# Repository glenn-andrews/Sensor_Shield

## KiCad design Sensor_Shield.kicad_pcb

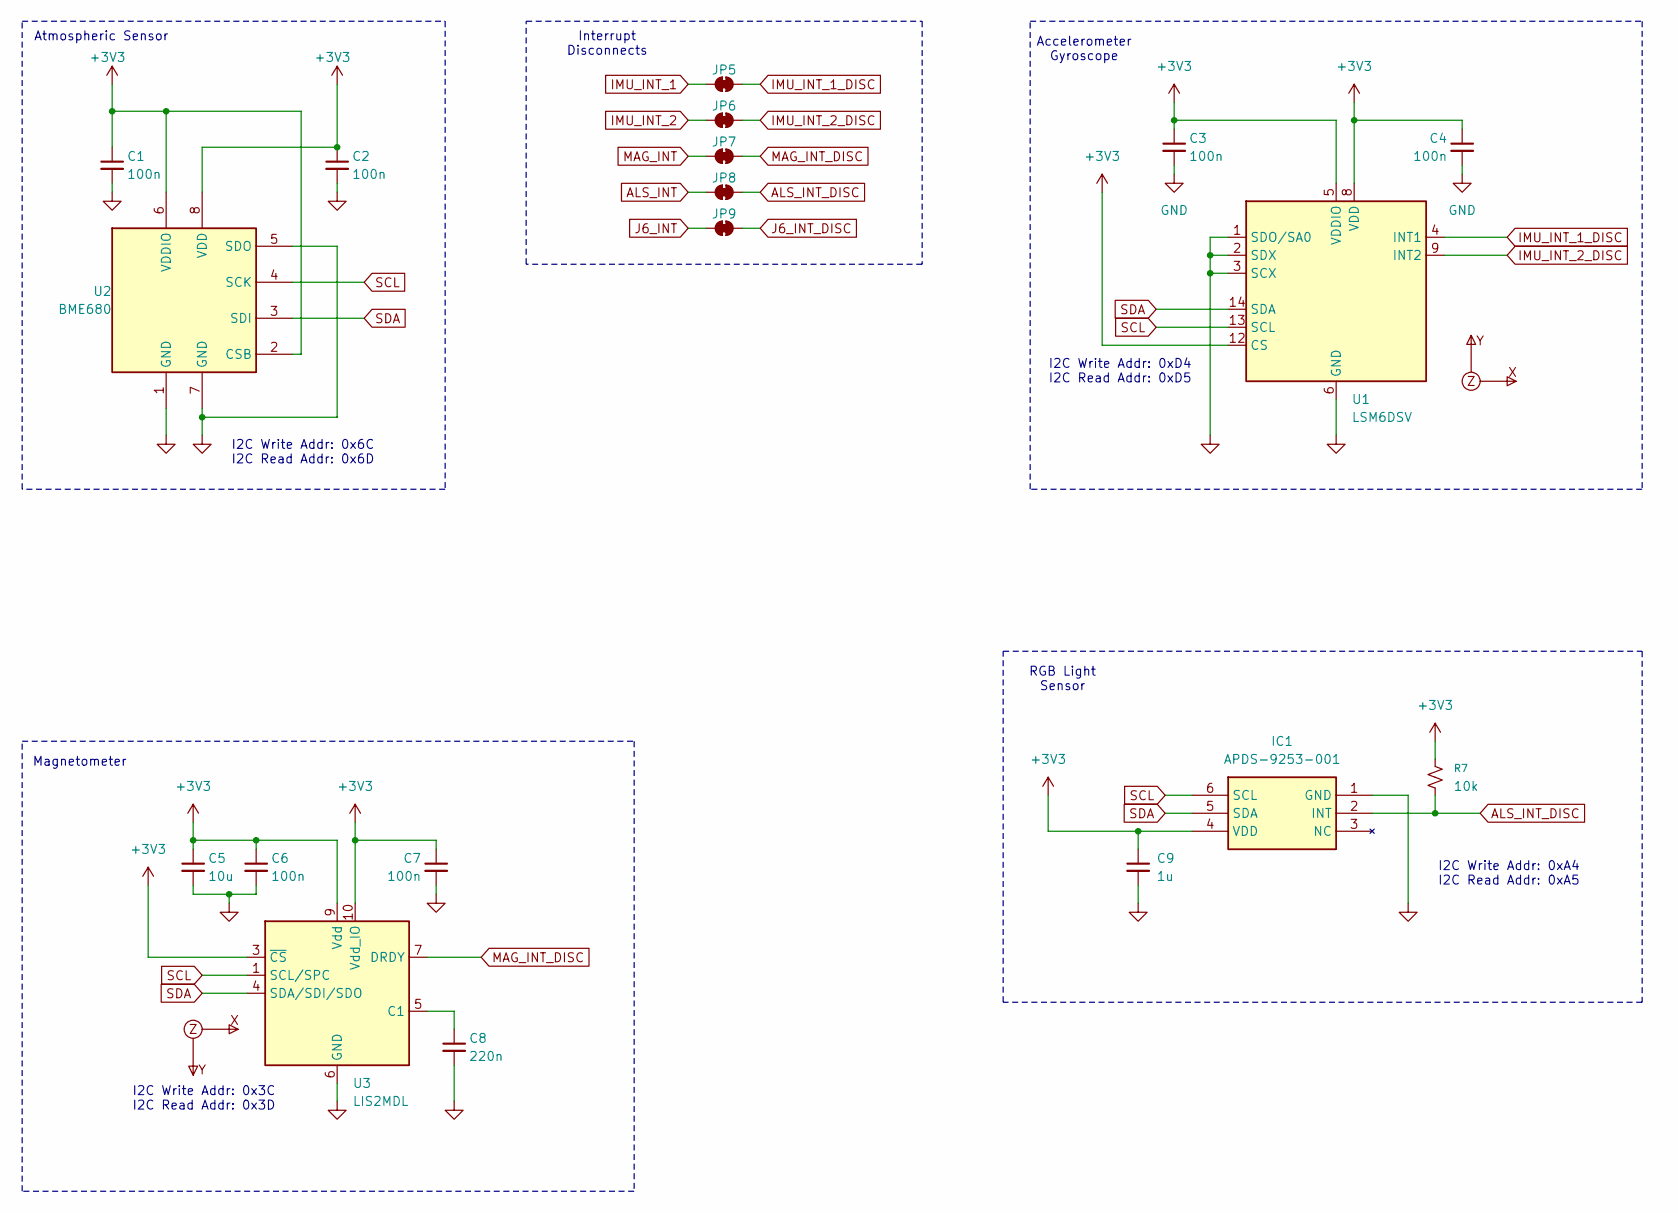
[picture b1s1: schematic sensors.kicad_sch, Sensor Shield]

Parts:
C1, C2, C3, C4, C6, C7: 100n; C_0402_1005Metric; Voltage 1kV; Tolerance 100%; MPN CL05A104KA5NNNC; Digi-Key PN 1276-1043-1-ND
C5: 10u; C_0805_2012Metric; Voltage 1kV; Tolerance 100%; MPN C0805C106K8PAC7210; Digi-Key PN 399-C0805C106K8PAC7210CT-ND
C8: 220n; C_0402_1005Metric; Voltage 1kV; Tolerance 100%; MPN CL05B224KO5NNNC; Digi-Key PN 1276-1176-1-ND
C9: 1u; C_0603_1608Metric; MPN C0603C105K4RACTU; Digi-Key PN 399-C0603C105K4RACTUCT-ND
IC1: APDS-9253-001; APDS9253001; Mouser Part Number 630-APDS-9253-001
JP5, JP6, JP7, JP8, JP9: Jumper_2_NC_Trace
R7: 10k; R_0402_1005Metric; MPN RC0402FR-0710KL; Digi-Key PN 311-10.0KLRCT-ND
U1: LSM6DSV; LGA-14_3x2.5mm_P0.5mm_LayoutBorder3x4y; MPN LSM6DSVTR; Digi-Key PN 497-LSM6DSVTRCT-ND
U2: BME680
U3: LIS2MDL; LGA-12_2x2mm_P0.5mm; MPN LIS2MDLTR; Digi-Key PN 497-17588-1-ND
U4: XYZ_Axes
U5: Mag_XYZ_Axes

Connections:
+3V3: C1.1, C2.1, C3.1, C4.1, C5.1, C6.1, C7.1, C9.1, IC1.4 (VDD), R7.2, U1.5 (VDDIO), U1.8 (VDD), U1.12 (CS), U2.2 (CSB), U2.6 (VDDIO), U2.8 (VDD), U3.3 (~CS), U3.9 (Vdd), U3.10 (Vdd_IO); also elsewhere on the board
ALS_INT: JP8.2 (B); also elsewhere on the board
ALS_INT_DISC: IC1.2 (INT), JP8.1 (A), R7.1
GND: C1.2, C2.2, C3.2, C4.2, C5.2, C6.2, C7.2, C8.2, C9.2, IC1.1 (GND), U1.1 (SDO/SA0), U1.2 (SDX), U1.3 (SCX), U1.6 (GND), U1.7 (GND), U2.1 (GND), U2.5 (SDO), U2.7 (GND), U3.6 (GND), U3.8 (GND); also elsewhere on the board
IMU_INT_1: JP5.2 (B); also elsewhere on the board
IMU_INT_1_DISC: JP5.1 (A), U1.4 (INT1)
IMU_INT_2: JP6.2 (B); also elsewhere on the board
IMU_INT_2_DISC: JP6.1 (A), U1.9 (INT2)
J6_INT: JP9.2 (B); also elsewhere on the board
J6_INT_DISC: JP9.1 (A); also elsewhere on the board
MAG_INT: JP7.2 (B); also elsewhere on the board
MAG_INT_DISC: JP7.1 (A), U3.7 (DRDY)
unnamed: C8.1, U3.5 (C1)
SCL: IC1.6 (SCL), U1.13 (SCL), U2.4 (SCK), U3.1 (SCL/SPC); also elsewhere on the board
SDA: IC1.5 (SDA), U1.14 (SDA), U2.3 (SDI), U3.4 (SDA/SDI/SDO); also elsewhere on the board

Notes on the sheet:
I2C Write Addr: 0xA4 I2C Read Addr: 0xA5
Accelerometer Gyroscope
I2C Write Addr: 0x3C I2C Read Addr: 0x3D
RGB Light Sensor
I2C Write Addr: 0x6C I2C Read Addr: 0x6D
I2C Write Addr: 0xD4 I2C Read Addr: 0xD5
Magnetometer
Atmospheric Sensor
Interrupt Disconnects

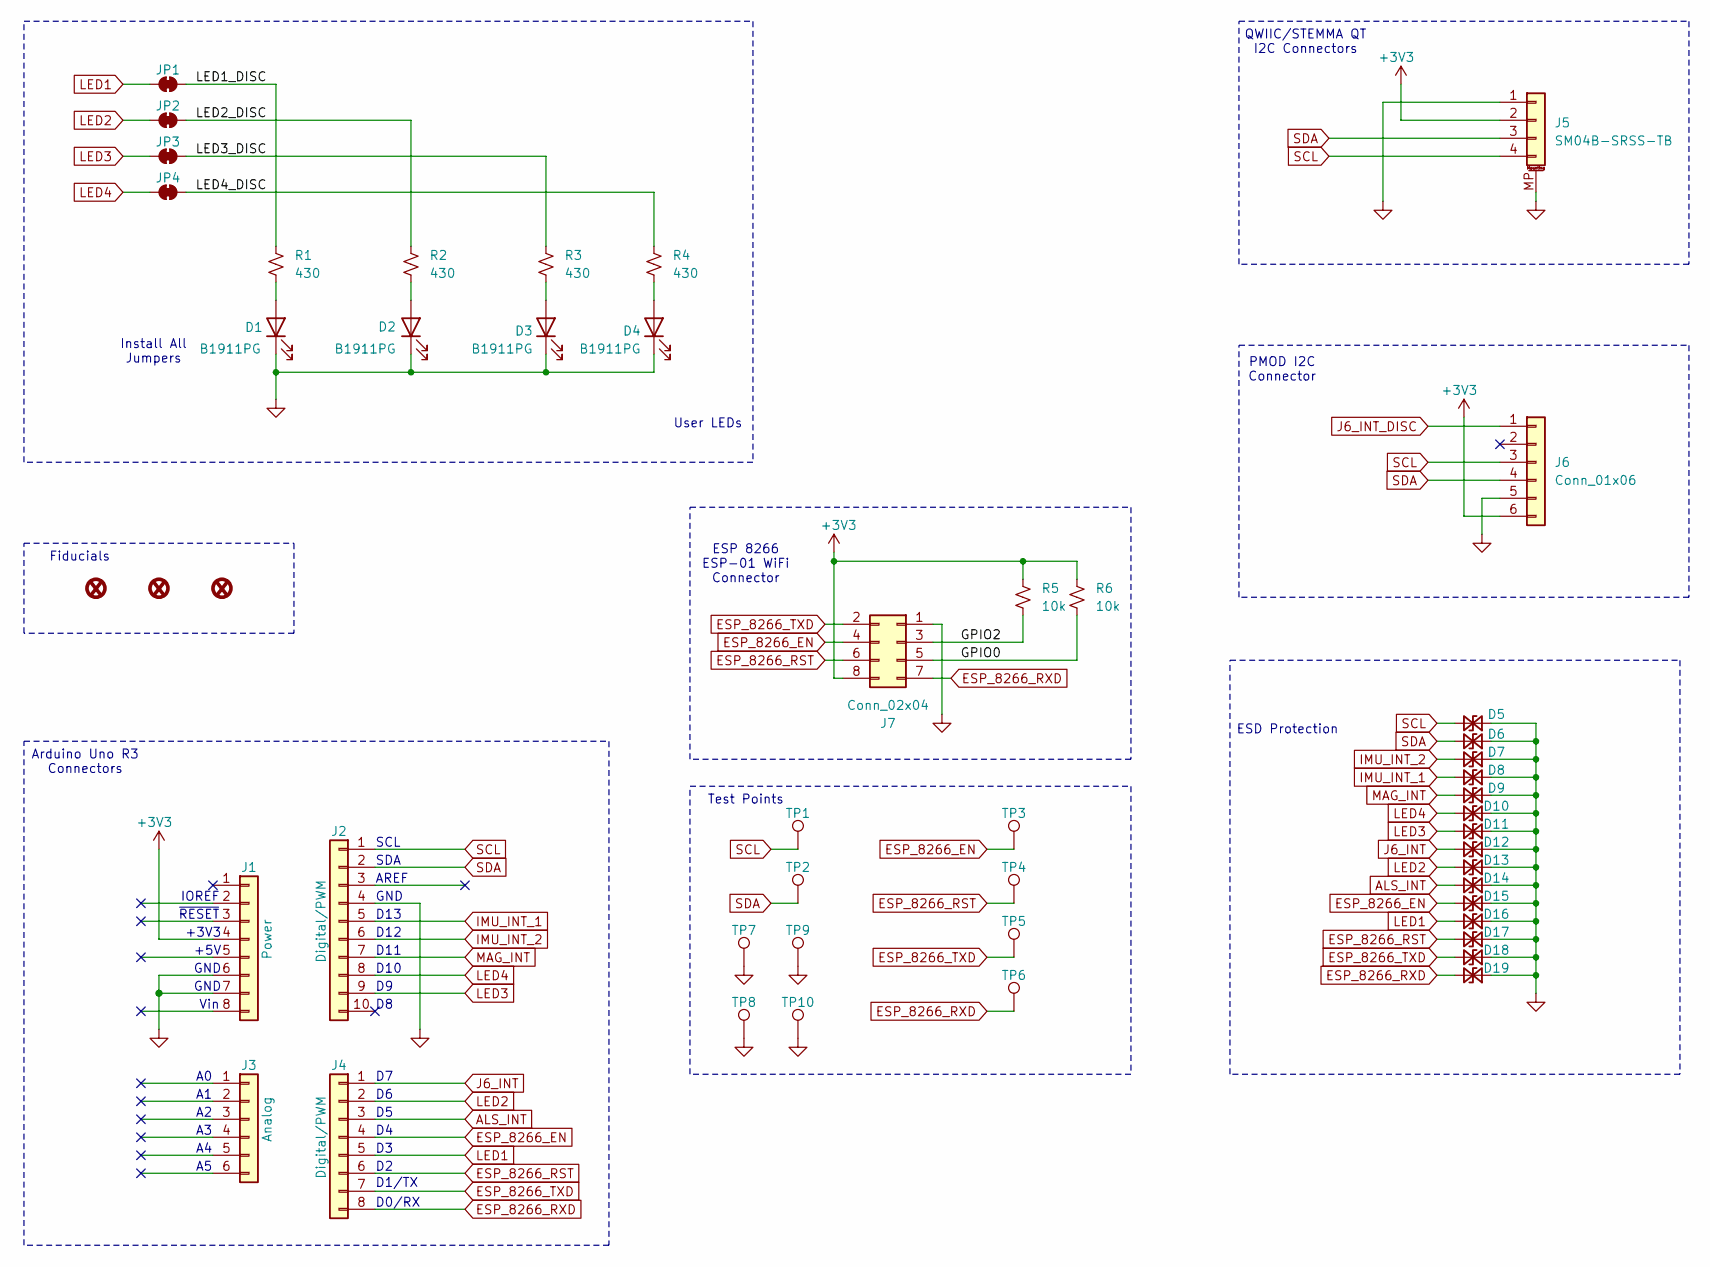
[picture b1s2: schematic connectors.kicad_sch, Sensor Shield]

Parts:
D1, D2, D3, D4: B1911PG; LED_0603_1608Metric; MPN B1911PG--20D000514U1930; Digi-Key PN 3147-B1911PG--20D000514U1930CT-ND
D5, D6, D7, D8, D9, D10, D11, D12, D13, D14, D15, D16, D17, D18, D19: D_TVS_Small; D_0402_1005Metric; MPN TPD1E10B06DPYR-EV; Digi-Key PN 5272-TPD1E10B06DPYR-EVCT-ND
FID1, FID2, FID3: Fiducial_0.5mm; Fiducial_0.5mm_Mask1mm
J1: Power; PinSocket_1x08_P2.54mm_Vertical; MPN 11417; Digi-Key PN 1568-11417-ND
J2: Digital/PWM; PinSocket_1x10_P2.54mm_Vertical; MPN 11417; Digi-Key PN 1568-11417-ND
J3: Analog; PinSocket_1x06_P2.54mm_Vertical; MPN 11417; Digi-Key PN 1568-11417-ND
J4: Digital/PWM; PinSocket_1x08_P2.54mm_Vertical; MPN 11417; Digi-Key PN 1568-11417-ND
J5: SM04B-SRSS-TB; JST_SH_SM04B-SRSS-TB_1x04-1MP_P1.00mm_Horizontal; MPN SM04B-SRSS-TB; Digi-Key PN 455-SM04B-SRSS-TBCT-ND
J6: Conn_01x06; PinSocket_1x06_P2.54mm_Horizontal_Flipped; MPN 613006143121; Digi-Key PN 732-613006143121-ND
J7: Conn_02x04; PinSocket_2x04_P2.54mm_Vertical; MPN 61300821821; Digi-Key PN 732-61300821821-ND
JP1, JP2, JP3, JP4: Jumper_2_NC_Trace
R1, R2, R3, R4: 430; R_0402_1005Metric; MPN RC0402FR-07430RL; Digi-Key PN 311-430LRCT-ND
R5, R6: 10k; R_0201_0603Metric; MPN RC0201FR-0710KL; Digi-Key PN 311-10.0KMCT-ND
TP1, TP2, TP3, TP4, TP5, TP6: 0.5mm; TestPoint-0.5mm
TP7, TP8, TP9, TP10: 1.25mm; TestPoint-1.0mm

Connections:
+3V3: J1.4, J5.2, J6.6, J7.8, R5.1, R6.1; also elsewhere on the board
/Connectors/GPIO0: J7.5, R6.2
/Connectors/GPIO2: J7.3, R5.2
/Connectors/LED1_DISC: JP1.2 (B), R1.1
/Connectors/LED2_DISC: JP2.2 (B), R2.1
/Connectors/LED3_DISC: JP3.2 (B), R3.1
/Connectors/LED4_DISC: JP4.2 (B), R4.1
ALS_INT: D14.2 (A2), J4.3; also elsewhere on the board
ESP_8266_EN: D15.2 (A2), J4.4, J7.4, TP3.1
ESP_8266_RST: D17.2 (A2), J4.6, J7.6, TP4.1
ESP_8266_RXD: D19.2 (A2), J4.8, J7.7, TP6.1
ESP_8266_TXD: D18.2 (A2), J4.7, J7.2, TP5.1
GND: D1.1 (K), D2.1 (K), D3.1 (K), D4.1 (K), D5.1 (A1), D6.1 (A1), D7.1 (A1), D8.1 (A1), D9.1 (A1), D10.1 (A1), D11.1 (A1), D12.1 (A1), D13.1 (A1), D14.1 (A1), D15.1 (A1), D16.1 (A1), D17.1 (A1), D18.1 (A1), D19.1 (A1), J1.6, J1.7, J2.4, J5.1, J5.MP (MountPin), J6.5, J7.1, TP7.1, TP8.1, TP9.1, TP10.1; also elsewhere on the board
IMU_INT_1: D8.2 (A2), J2.5; also elsewhere on the board
IMU_INT_2: D7.2 (A2), J2.6; also elsewhere on the board
J6_INT: D12.2 (A2), J4.1; also elsewhere on the board
J6_INT_DISC: J6.1; also elsewhere on the board
LED1: D16.2 (A2), J4.5, JP1.1 (A)
LED2: D13.2 (A2), J4.2, JP2.1 (A)
LED3: D11.2 (A2), J2.9, JP3.1 (A)
LED4: D10.2 (A2), J2.8, JP4.1 (A)
MAG_INT: D9.2 (A2), J2.7; also elsewhere on the board
unnamed: D1.2 (A), R1.2
unnamed: D2.2 (A), R2.2
unnamed: D3.2 (A), R3.2
unnamed: D4.2 (A), R4.2
SCL: D5.2 (A2), J2.1, J5.4, J6.3, TP1.1; also elsewhere on the board
SDA: D6.2 (A2), J2.2, J5.3, J6.4, TP2.1; also elsewhere on the board

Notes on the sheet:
QWIIC/STEMMA QT I2C Connectors
IOREF
GND
SDA
Fiducials
D11
SCL
ESD Protection
D12
Install All Jumpers
ESP 8266 ESP-01 WiFi Connector
PMOD I2C Connector
Vin
User LEDs
+5V
D0/RX
Test Points
AREF
Arduino Uno R3 Connectors
D13
+3V3
D1/TX
D10
~{RESET}

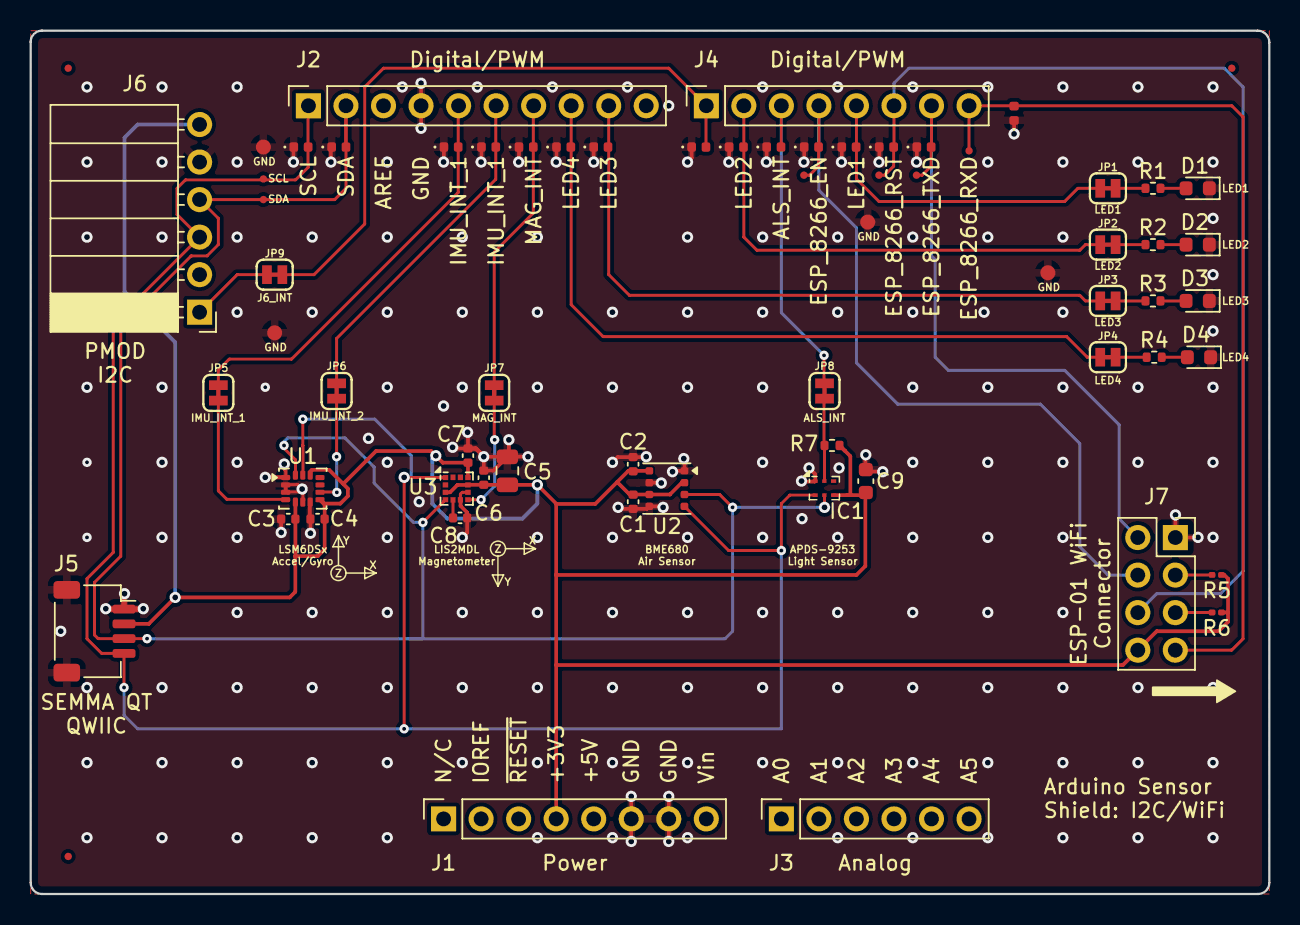
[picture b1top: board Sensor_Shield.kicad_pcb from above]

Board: 2 copper layers, 83.8 x 58.4 mm, 70 parts (0 on the bottom side), 33 nets.

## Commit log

2026-01-01 Checking In Project
    Initial check-in of working files
